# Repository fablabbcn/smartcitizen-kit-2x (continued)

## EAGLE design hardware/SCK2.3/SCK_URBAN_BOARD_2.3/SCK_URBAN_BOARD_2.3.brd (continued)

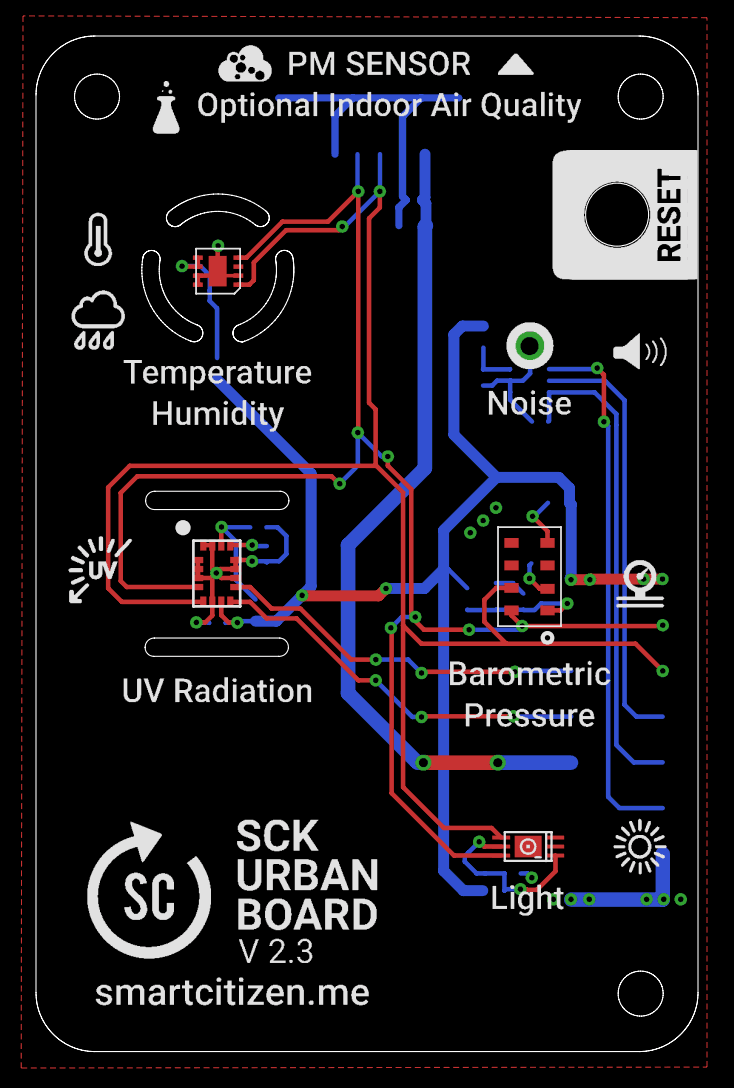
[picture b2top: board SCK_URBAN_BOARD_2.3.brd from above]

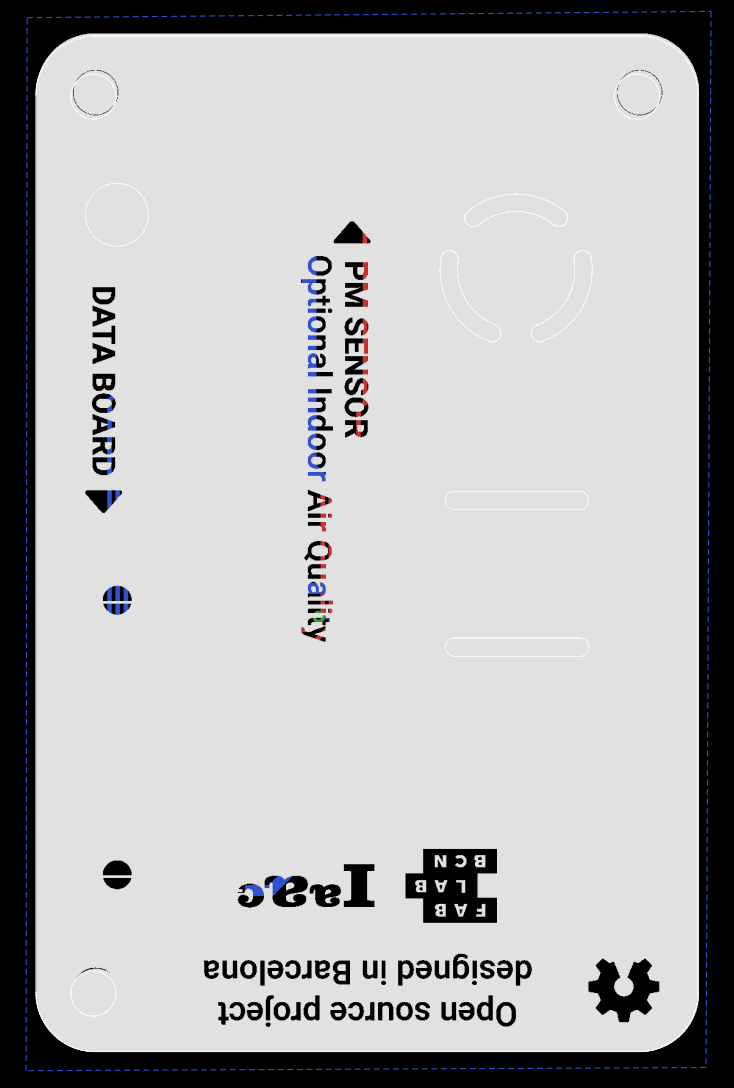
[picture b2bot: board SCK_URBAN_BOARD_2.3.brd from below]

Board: 2 copper layers, 36.8 x 56.4 mm, 26 parts (22 on the bottom side), 18 nets.

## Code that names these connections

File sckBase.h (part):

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 	-------------------------------
*/
// ESP8266 Management
#define CH_PD   		31		// PB23
#define POWER_WIFI  	30		// PB22
#define GPIO0   		11		// PA16
#define CS_ESP  		13		// PA17

// RGB Led 
#define PIN_LED_RED 	6		// PA20
#define PIN_LED_GREEN 	12		// PA19
#define PIN_LED_BLUE 	10		// PA18

// Button 
#define PIN_BUTTON 		7		// PA21

// Sensor Board Conector
#define IO0 9					// PA7 -- CO Sensor Heather
#define IO1 8       			// PA6 -- NO2 Sensor Heater
#define IO2 3					// PA9 -- Unused
#define IO3 4					// PA8 -- Unused
#define S0 A3         			// PA4 -- CO Sensor
#define S1 A4         			// PA5 -- NO2 Sensor
#define S2 A1         			// PB8 -- CO Current Sensor
#define S3 A2         			// PB9 -- NO2 Current Sensor
#define S4 A5         			// PB2 -- Sound Sensor
#define S5 A0         			// PA2 -- Unused

// SPI Configuration
#define MOSI 	21				// PB10
#define SCK 	20				// PB11
#define MISO	18				// PA12
#define CS_SDCARD	2			// PA14 -- SPI Select SDcard

// Power Management
#define PS 	38					// PA13 -- TPS63001 PS/SYNC

// ACOMODAR Y CAMBIAR NOMBRES ESTO ES TEMP
#define POT1                 0x50    
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
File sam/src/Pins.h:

#pragma once

// Button
const uint8_t pinBUTTON = 7;            // PA21

// RGB Led pins
const uint8_t pinRED    = 6;            // PA20
const uint8_t pinGREEN  = 12;           // PA19
const uint8_t pinBLUE   = 10;           // PA18

// Other leds
const uint8_t pinLED_USB = 26;          // PA27 -- Usb Serial Led

// ESP pins
const uint8_t pinPOWER_ESP =    30;     // PB22 -- ESP power
const uint8_t pinESP_TX_WIFI =  17;     // PA04 -- WiFi TX Serial -- SERCOM0:PAD[0]
const uint8_t pinESP_RX_WIFI =  18;         // PA05 -- WiFi RX Serial -- SERCOM0:PAD[1]
const uint8_t pinESP_GPIO0 =    16;     // PB09 -- ESP GPIO0
const uint8_t pinESP_CH_PD =    15;     // PB08 -- ESP CHPD

// Power management
const uint8_t pinMEASURE_BATT = 14;     // PA02 -- Battery analog level
const uint8_t pinCHARGER_INT =  42;     // PA03 -- Charger interrupt

// Sdcard
const uint8_t pinCARD_DETECT = 5;       // PA15 -- Card detect
const uint8_t pinCS_SDCARD = 2;         // PA14 -- SPI Select SDcard
const uint8_t pinCS_FLASH = 38;         // PA13 -- SPI Select Flash

// I2C internal bus
const uint8_t pinWIRE_SDA = 20;         // PA22 -- SDA_A
const uint8_t pinWIRE_SCL = 21;         // PA23 -- SCL_A

// Auxiliary I2C bus
const uint8_t pinPOWER_AUX_WIRE = 31;       // PB23 -- Power Auxiliary I2C bus
const uint8_t pinAUX_WIRE_SDA = 11;     // PA16 -- Auxiliary I2C SDA -- SERCOM1:PAD[0]
const uint8_t pinAUX_WIRE_SCL = 13;     // PA17 -- Auxiliary I2C SCL -- SERCOM1:PAD[1]

// I2S bus
const uint8_t pinI2S_SCK = 1;           // PA10 -- I2S_SCK
const uint8_t pinI2S_SD = 9;            // PA07 -- I2S_SD
const uint8_t pinI2S_FS = 0;            // PA11 -- I2S_FS

// PMS sensor
const uint8_t pinPM_ENABLE = 8;         // PA06 -- Enable PMS step up power (active HIGH)

// BOARD CONNECTOR
const uint8_t pinBOARD_CONN_3 = 3;      // PA09 -- Free 1
const uint8_t pinBOARD_CONN_4 = pinWIRE_SCL;    // PA23 -- SCL_A
const uint8_t pinBOARD_CONN_5 = 4;      // PA08 -- Free 2
const uint8_t pinBOARD_CONN_6 = pinWIRE_SDA;    // PA22 -- SDA_A
const uint8_t pinBOARD_CONN_7 = 27;     // PA28 -- Free 3
const uint8_t pinBOARD_CONN_8 = pinI2S_SCK; // PA10 -- I2S_SCK
// const uint8_t pinBOARD_CONN_9 =      // 5v/1.5A Line
const uint8_t pinBOARD_CONN_10 = pinI2S_SD; // PA07 -- I2S_SD
const uint8_t pinBOARD_CONN_11 = 25;        // PB03 -- RX_PMS -- PMS RX Serial -- SERCOM_ALT5:PAD[1]
const uint8_t pinBOARD_CONN_12 = pinI2S_FS; // PA11 -- I2S_FS
const uint8_t pinBOARD_CONN_13 = 19;        // PB02 -- TX_PMS -- PMS TX Serial -- SERCOM_ALT5:PAD[0]

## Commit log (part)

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2023-04-18 Side by side buttons in esp setup
2023-04-18 Upgrade deprecated gulp modules names
2023-05-11 Fix Atlas EC not receiving all data on very long readings
2023-05-11 Fix Atlas temperature compensation not using DS18B20 sensor
2023-05-16 Add PMS5003 PN Count IDs
2023-05-18 Implemented initial support for SPS30
2023-05-18 Urban code cleanUp
2023-05-18 Improved Urban board startup
2023-05-18 Fix startup hang on External SHT Temp/Hum sensor
2023-05-23 SPS30 Fixes and improvements
2023-05-23 SPS30 sleep function is n ow public (missing in last commit)
2023-05-23 Initial SEN5X implementation
2023-05-23 Don't print error message when urban board sensors are not detected
2023-05-23 Fix PM not sending proper sensor state after urgan getReading() refactor
2023-05-23 Retab and cleanUp
2023-05-23 Added platform Id's to SEN5X metrics
2023-05-23 Fix on Sensirion lib not detecting SAMD I2C size
2023-05-23 Fix detection for SEN5X models
2023-05-23 First iteration of full metric support on SEN54 and SEN55
2023-05-30 Implemented auxiliary SFA30 Formaldehyde Sensor Module
2023-06-01 Updated gitignore
2023-06-02 Added SFA30 platfor id's and fixed some start issues on the same sensor.
2023-06-08 Implemented SEN5X without any external dependency
2023-06-08 Really merge SEN5X new code
2023-06-12 Added defines to disable sensors on build to save RAM
2023-06-13 Avoid SEN5X to trigger cleaning after new firmware upload.
2023-06-15 SPS30 manage celan interval, some touches to SEN5X and SPS30
2023-06-16 Improved RAM management
2023-06-16 Hardware info now contains last reset cause
2023-06-22 Implemented RSSI WiFi signal as a sensor
2023-06-26 Cleaned up make.py help message
2023-07-05 Updated arduino core
2023-07-05 Updated tools submodule
2023-07-05 Hardware info now contains git branch, info file is now json format
2023-07-05 Updated platformio.ini lib_deps syntax
2023-07-06 Updated led code, brightness can be adjusted, breathing while booting to detect hangs
2023-07-06 Missing from led brightness commit
2023-07-06 SD card work: updated lib, file manager functions
2023-07-10 Sd card code refurbished, file manager functions working
2023-07-10 Fix led not updating on STATIC mode
2023-07-11 Moved BME68X to Urban Board Sensors
2023-07-11 BME68X details
2023-07-14 SEN5X sensor now saves VOCS state and restores it when needed
2023-07-17 Added platform ID to several sensors
2023-07-17 Removed sensor control property, wasn't used
2023-07-18 Removed Arduino String from sensor functions
2023-07-24 Add LPS33 Barometric pressure sensor
2023-07-31 AS7331 initial iplementation, still WIP
2023-07-31 Some touches to SEN5X
2023-10-19 ifdef disable CCS811 and comment on fix compiling
2023-10-19 SEN5X cleaning is not triggered if time is not set
2023-10-23 Save and restore VOC state correctly
2023-10-23 SEN5X monitor mode is now working properly
2023-10-23 Always publish to shell SEN5X model
2023-10-24 Finished AS7331 implementation
2023-10-24 Updated test protocol for SCK 2.2
2023-10-27 Add bugfix branch while sparkfun CCS811 PR is not merged
2023-10-27 Fix missing ifdef for SEN5X init
2023-10-30 Rename Sck_PM to Sck_PMS to avoid confusion
2023-10-30 Add ifdefs for pressure sensors and rename MPL
2023-10-30 Minor cosmetic change
2023-10-30 Minor cosmetic changes and trailspace cleanup
2023-10-30 Base configuration for TA
2023-10-30 Urban Sensors 2.2 and datasheet fix for LPS33
2023-11-06 Add build workflow
2023-11-06 Add submodules
2023-11-07 Enable automation in dev branch
2023-11-07 Update tools submodule
2023-11-07 Remove cached from platformio
2023-11-14 Change LPS Sensor name for consistency
2023-11-14 Finalise test protocol for SCK2.2
2023-11-17 Add variants to compiling process
2023-11-17 Change build process in workflow
2023-11-20 Check building process in various platforms.
2023-11-27 Fix missing csv speed file update to new sckfile model
2023-12-20 Default activated sensors per env
2023-12-20 Minor typo
2023-12-21 Hardware version now based on env define
2024-02-27 Sensirion libs are now fixed to last version
2024-02-27 SEN5X: VOC's and NOX's are now disabled by default
2024-02-27 SEN5X: New continous mode when VOC's or NOX's are enabled
2024-02-27 SEN5X: sensors are now automatically enabled/disabled and its interval changed in groups: PM, PN, TH, VOC and NOX
2024-02-27 SEN5X: if reading interval is smaller than warmUp continous mode is enabled
2024-02-29 Add option for compiling to .hex
2024-02-29 Add env for test firmware. Change define
2024-02-29 Minor fix on aux wire test firmware output
2024-02-29 Add hardware for SCK2.2
2024-03-01 Add the possibility to flash other bootloaders based on Makefile.user
2024-03-01 Update bootloader submodule
2024-03-05 Enforce reset after using shell mode to get a clean state
2024-03-05 Make ESP error visible to the user
2024-04-23 Minor fix in hardware Readme
2024-05-17 Only send compensation in atlas sensors when needed
2024-05-27 Add temperature and humidity corrections for all modes and depending on SCK21 or SCK22
2024-05-29 Improve corrections for temperature and relative humidity, also in sd card mode
2024-06-03 Improve T correction of 2.1
2024-06-06 Only send temperature command if temperature reading is valid
2024-07-24 Hardware files for SCK2.3 - WIP
2024-08-21 Bump sam and esp version to 0.9.9
2024-09-10 Add SCK2.3
2024-09-10 Reorganize hardware files and fix readme
2024-10-04 Atlas delay should be sufficient after transmission is ended to avoid non-ready data
2024-10-04 Add sleep wakeup to atlas drivers and avoid erroneous data on wake
2024-10-23 Expose STA MAC address along with softAP one
2024-10-28 Remove seeduino test plan
2024-10-28 Revert delay position. Increment to shortwait
2024-10-28 WIP tcomp command for atlas sensors
2024-10-28 Add commands to enable temperature compensation on atlas sensors
2024-11-08 Pio env now on info hash
2024-11-08 Revert "Enhancement/pio env info"
2024-11-20 Turn off all SEN5X metrics when button is down.
2024-11-20 Improve output of debug commands
2024-11-21 Fix ifdefs for external temperature sensor
2024-11-25 Minor fix on output of atlas control sensor command
2024-12-09 Bump to 0.9.10
2024-12-12 Update test plan and remove unused #define
2025-01-31 Improve make.py to avoid flashing when building firmware fails
2025-02-13 Minor fix on make.py
2025-03-25 Urban Board Silkscreen
2025-07-17 Update README.md
    Replacing the SCK welcome README with DaphiSensor README
2025-07-21 Remove ADS1X15 fork
    Remove the fork as adafruit has refurbished it and we do not need a fork for this anymore. They can now pass a Wire object to the begin.
2025-08-01 Create Hardware Overview
    Some important details about the hardware in use
2025-08-01 Add file extension to the file name
2025-08-01 Update Hardware Overview.md
    fix typos
2025-08-01 Update README.md
    updated with new links and information to guidelines and hardware overview
2025-08-07 Fix VOCstate buffer size bug and add model checks
    * Fixes size for VOC state accounting for CRC
    * Adds checks for model version clash
2025-08-10 Add .clang-format and .clang-tidy configuration files
2025-08-10 Add Docker setup and scripts for clang-tidy and clang-format checks
2025-08-11 Update README.md
    Changed references to the wiki
2025-08-11 Delete guides and manuals directory
    Content is now in the Wiki
2025-08-12 Add CI job for Clang format and tidy checks
2025-08-12 added .ino files to the checks
2025-08-12 test file to test autmoted checks
2025-08-12 Update clang check script paths in CI workflow and README
2025-08-12 Refactor clang checks to only format and analyze changed files
2025-08-12 Change submodule checkout to false in clang checks workflow
2025-08-12 test file to test the checks
2025-08-12 update git fetch command in CI workflow
2025-08-12 update clang-tidy command to treat warnings as errors
2025-08-12 removed tests.cpp for testing
2025-08-18 Update README.md
    Fixed broken links
2025-08-26 Typical particle size is not in #/cm3 - remove convertion
2025-09-03 Fix continuous mode readings
    If continuous mode is activated most SEN5X readings went wrong because
    the already read values weren't returned but get_reading() returned an
    error state. By checking if update() failed because of no new values
    available in continuous mode (SEN54 and SEN55) we can return the stored
    values safely.
2025-09-09 Only check pio environments when needed
2025-09-09 Add forced continuous mode to check
2025-09-09 Add forced continuous mode
2025-09-09 Test on SCK reboot for retrieving VOC state from sensor
2025-09-10 Move vocStateFromSensor and improve debug
2025-09-10 Minor improvements on debug
2025-09-10 Add valid flag and timestamp on VOCState function
2025-09-12 Attempt at making first VOC reading not reported
2025-09-12 Fix returned buffer on VOCstate as it doesn't include CRC
2025-09-16 Add RHT/Gas only mode to SEN55
2025-09-18 Upgrade ads1x15 library
2025-09-18 Add SHT31 in external sensor name to allow parsing of commands
2025-09-18 Minor comment
2025-09-18 Minor typo in units
2025-09-18 Fix humidity offset type
2025-09-18 Create interface for SHT31 custom calibration
2025-09-18 Adds rht calibration to external sensors
    * Minor fixes in WITH_RANGE define
    * Adds clear command to reset calibration to default
2025-09-18 Fix not taking oled defaults
2025-09-22 Minor fix for non urban setups
2025-09-23 Change default sensor enables for SEN54 and SEN55
2025-09-25 Change default sensor enables for SEN54 and SEN55 Bump SAM version
2025-10-12 Fix upload script for newer Python version
2025-10-12 Disable softAP during startup
    To avoid a default popup WiFi network during ESP startup we explicitly
    disable it as early as possible.
2025-10-14 Fix shell parameter parsing
    It doesn't make sense to parse more tokens if the current one fails.
    TODO: Word in input should match a complete word in title and not just a
    substring.
2025-11-27 Fix sensor name for AS7331 UVC in Sensors.h
2026-01-07 Remove screen flag from platformio.ini
2026-01-07 Fix links in readme
2026-05-11 Add defines on test firmware
2026-05-12 Fix URL formatting for Adafruit ADS1X15 library
2026-05-12 Update gitignore
2026-05-12 Add env variables for testing procedure
2026-05-12 Add .internal to gitignore
2026-05-12 Make.py more robust
2026-05-12 Add fake credentials for tests
2026-05-12 Stop tracking .seeed and .internal
2026-05-12 Add .seeed file with WiFi credentials
2026-05-12 Add internal configuration for WiFi credentials
2026-05-12 Remove files again
2026-05-12 Add defaults to test credentials on env.py
2026-05-12 Fix on env.py
2026-05-18 Upgrade espressiff platform
    * Provides access to retry functions and password error checking
2026-05-18 Add constants with SC_ and uppercase
2026-05-18 Always retry SC_MAX_WIFI_RETRIES on Wi-Fi connection attempts
2026-05-18 Make sure espON flag is true after booting ESP
2026-05-18 Add new case for password error on ESP
2026-05-18 Set AutoReconnect to true on ESP after trying connection
2026-05-18 Rename mqttHellow to mqttHello
2026-05-18 Fix typo detected by pral2a/Claudio on other PR
2026-05-18 Replace "!!!" on error logs. Make error logs consistent
2026-05-18 More error logs
2026-05-18 Make switch-case statement consistent with brackets
2026-05-18 Experimental: add yield() statements on potentially blocking NTP requests
2026-05-18 Coding style and linting changes
2026-05-18 Fix error reported by Claudio and pral2a
2026-05-21 Fix image link just for fun and enhance forum support information
    Updated image link and improved forum support text.
2026-05-21 Correct image syntax in README.md
    Fix image link formatting in README
2026-05-21 Update image in README with new version photo
2026-05-22 Add potential chanes commented, not showing improvement
